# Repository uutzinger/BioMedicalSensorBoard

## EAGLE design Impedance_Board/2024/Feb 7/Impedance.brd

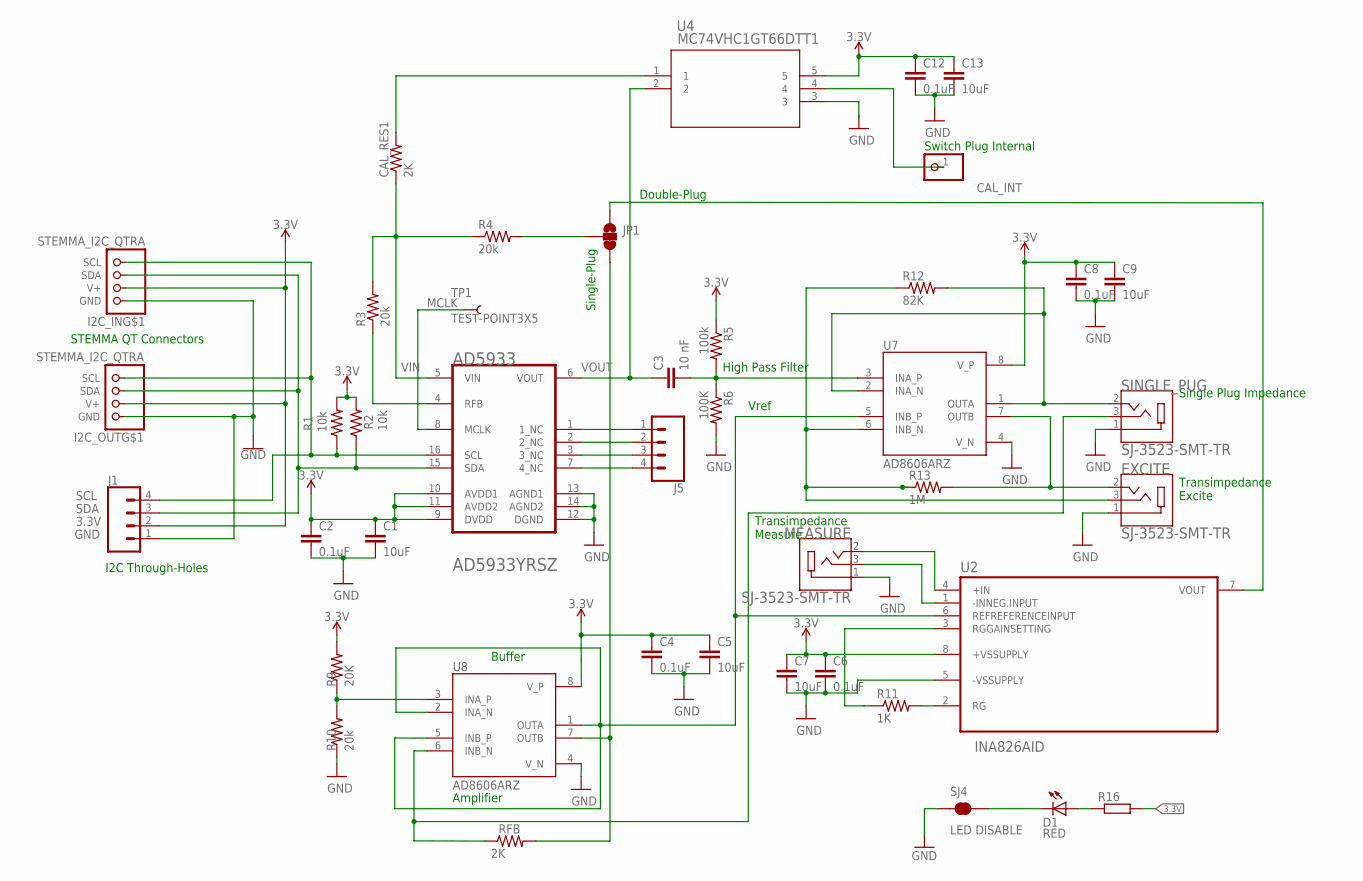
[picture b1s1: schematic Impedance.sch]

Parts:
AD5933: ANALOG_DEVICES_AD5933YRSZANALOG_DEVICES_AD5933YRS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; ANALOG_DEVICES_AD5933YRSZ_0
C1, C5, C7, C9, C13: 10uF; C0603
C2, C4, C6, C8, C12: 0.1uF; C0603
C3: 10 nF; C0603
CAL_INT: PINHD-1X1; 1X01
CAL_RES1: 2K; R0603
D1: RED; LED-0603
EXCITE: SJ-3523-SMT-TR; CUI_SJ-3523-SMT-TR
I2C_IN, I2C_OUT: STEMMA_I2C_QTRA; JST_SH4_RA
J1, J5: CONN_04; 1X04
JP1: JUMPER-SMT_3_1-NC_TRACE_NO-SILK; SMT-JUMPER_3_1-NC_TRACE_NO-SILK
MEASURE: SJ-3523-SMT-TR; CUI_SJ-3523-SMT-TR
R1, R2: 10k; R0603
R3, R4, R10: 20k; R0603
R5: 100k; R0603
R6: 100K; R0603
R9: 20K; R0603
R11: 1K; R0603
R12: 82K; R0603
R13: 1M; R0603
R16: R__0603; R0603
RFB: 2K; R0603
SINGLE_PUG: SJ-3523-SMT-TR; CUI_SJ-3523-SMT-TR
SJ4: LED DISABLE; SMT-JUMPER_2_NC_TRACE_NO-SILK
TP1: TEST-POINT3X5; PAD.03X.05
U2: INA826AID; SOIC127P599X175-8N
U4: MC74VHC1GT66DTT1; TSOP5_1P65X3P15_ONS
U7, U8: AD8606ARZ; SOIC127P600X175-8N

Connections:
3.3V: AD5933.9 (DVDD), AD5933.10 (AVDD1), AD5933.11 (AVDD2), C1.1, C2.1, C4.1, C5.1, C6.1, C7.1, C8.1, C9.1, C12.1, C13.1, I2C_IN.2 (V+), I2C_OUT.2 (V+), J1.2, R1.2, R2.2, R5.1, R9.2, R16.2, U2.8 (+VSSUPPLY), U4.5, U7.8 (V_P), U8.8 (V_P)
GND: AD5933.12 (DGND), AD5933.13 (AGND1), AD5933.14 (AGND2), C1.2, C2.2, C4.2, C5.2, C6.2, C7.2, C8.2, C9.2, C12.2, C13.2, EXCITE.1, I2C_IN.1 (GND), I2C_OUT.1 (GND), J1.1, MEASURE.1, R6.2, R10.1, SINGLE_PUG.1, SJ4.1, U2.5 (-VSSUPPLY), U4.3, U7.4 (V_N), U8.4 (V_N)
MCLK: AD5933.8 (MCLK), TP1.P$1
unnamed: JP1.2, R4.2
unnamed: CAL_INT.1, U4.4
unnamed: AD5933.1 (1_NC), J5.1
unnamed: AD5933.2 (2_NC), J5.2
unnamed: AD5933.4 (RFB), R3.1
unnamed: RFB.2, U8.7 (OUTB)
unnamed: C3.2, R5.2, R6.1, U7.3 (INA_P)
unnamed: AD5933.3 (3_NC), J5.3
unnamed: AD5933.7 (4_NC), J5.4
unnamed: U2.6 (REFREFERENCEINPUT), U7.5 (INB_P), U8.1 (OUTA), U8.2 (INA_N), U8.5 (INB_P)
unnamed: R9.1, R10.2, U8.3 (INA_P)
unnamed: R12.2, SINGLE_PUG.2, U7.1 (OUTA), U7.2 (INA_N)
unnamed: R11.1, U2.3 (RGGAINSETTING)
unnamed: RFB.1, SINGLE_PUG.3, U8.6 (INB_N)
unnamed: R11.2, U2.2 (RG)
unnamed: EXCITE.2, R13.2, U7.7 (OUTB)
unnamed: MEASURE.2, U2.4 (+IN)
unnamed: MEASURE.3, U2.1 (-INNEG.INPUT)
unnamed: EXCITE.3, R12.1, R13.1, U7.6 (INB_N)
unnamed: CAL_RES1.2, U4.1
unnamed: JP1.1, U2.7 (VOUT)
unnamed: D1.A, R16.1
unnamed: D1.C, SJ4.2
SCL: AD5933.16 (SCL), I2C_IN.4 (SCL), I2C_OUT.4 (SCL), J1.4, R1.1
SDA: AD5933.15 (SDA), I2C_IN.3 (SDA), I2C_OUT.3 (SDA), J1.3, R2.1
VIN: AD5933.5 (VIN), CAL_RES1.1, R3.2, R4.1
VOUT: AD5933.6 (VOUT), C3.1, U4.2

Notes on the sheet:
High Pass Filter
Vref
Transimpedance Measure
Transimpedance Excite
Single Plug Impedance
Amplifier
Buffer
STEMMA QT Connectors
I2C Through-Holes
Single-Plug
Double-Plug
Switch Plug Internal

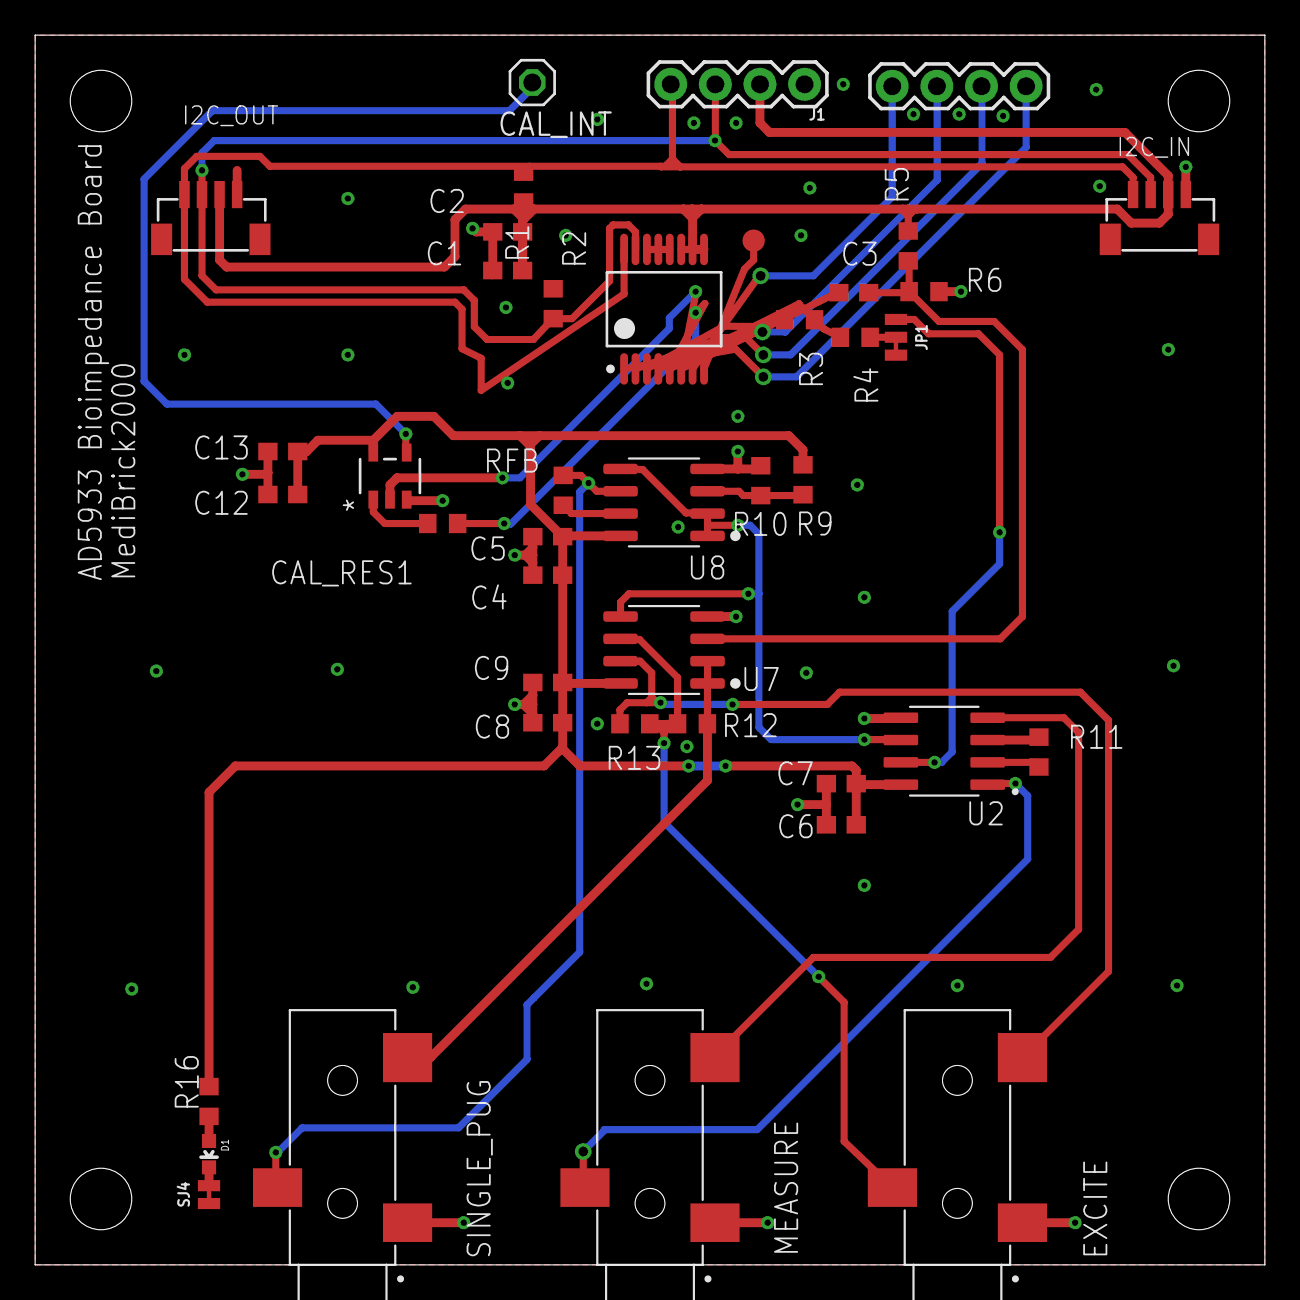
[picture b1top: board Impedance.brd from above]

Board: 2 copper layers, 70.0 x 70.0 mm, 42 parts (0 on the bottom side), 30 nets.

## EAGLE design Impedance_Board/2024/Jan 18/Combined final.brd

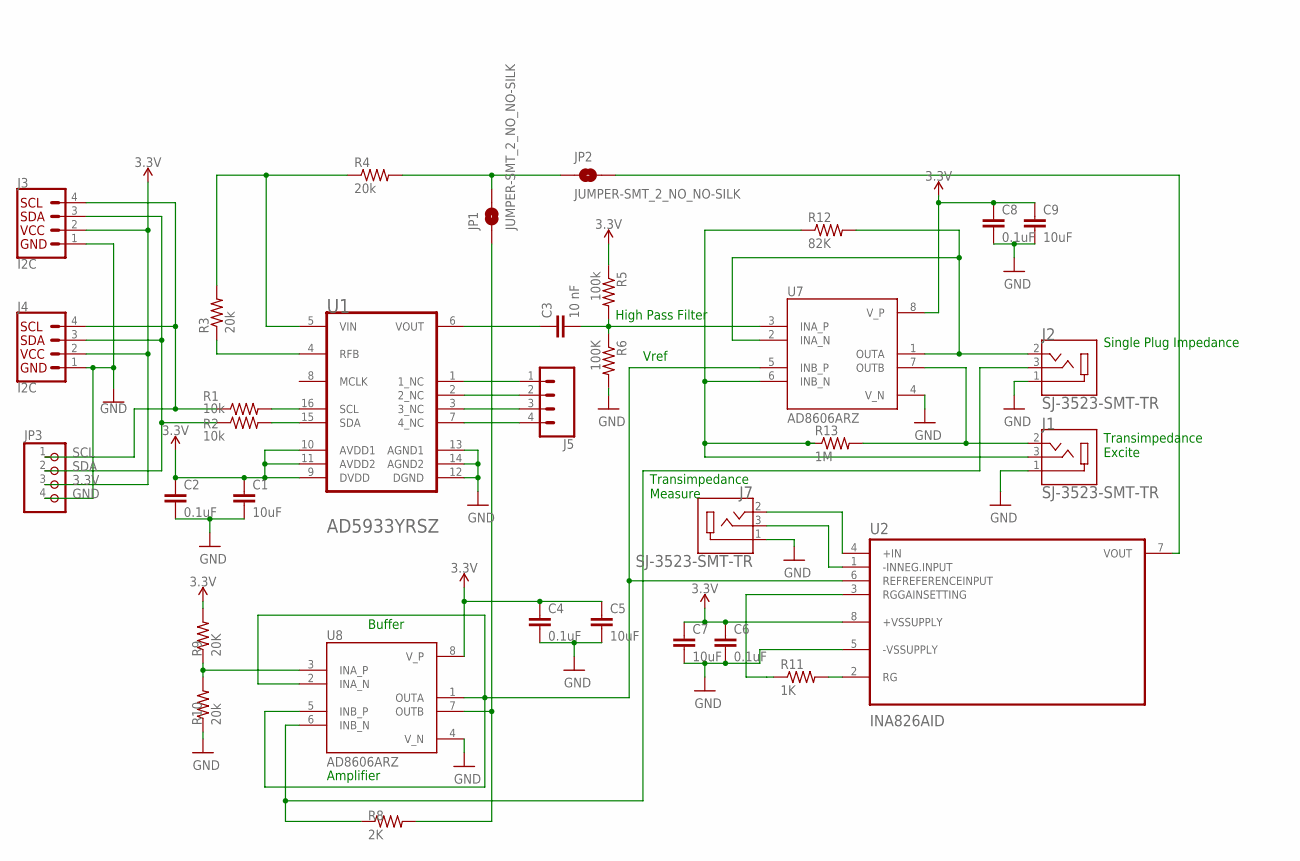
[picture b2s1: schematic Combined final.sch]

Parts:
C1, C5, C7, C9: 10uF; C0603
C2, C4, C6, C8: 0.1uF; C0603
C3: 10 nF; C0603
J1, J2, J7: SJ-3523-SMT-TR; CUI_SJ-3523-SMT-TR
J3, J4: I2C; JST04_1MM_RA
J5: CONN_04; 1X04
JP1, JP2: JUMPER-SMT_2_NO_NO-SILK; SMT-JUMPER_2_NO_NO-SILK
JP3: PINHD-1X4; 1X04
R1, R2: 10k; R0603
R3, R4, R10: 20k; R0603
R5: 100k; R0603
R6: 100K; R0603
R8: 2K; R0603
R9: 20K; R0603
R11: 1K; R0603
R12: 82K; R0603
R13: 1M; R0603
U1: ANALOG_DEVICES_AD5933YRSZANALOG_DEVICES_AD5933YRS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; ANALOG_DEVICES_AD5933YRSZ_0
U2: INA826AID; SOIC127P599X175-8N
U7, U8: AD8606ARZ; SOIC127P600X175-8N

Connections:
3.3V: C1.1, C2.1, C4.1, C5.1, C6.1, C7.1, C8.1, C9.1, J3.2, J4.2, JP3.3, R5.1, R9.2, U1.9 (DVDD), U1.10 (AVDD1), U1.11 (AVDD2), U2.8 (+VSSUPPLY), U7.8 (V_P), U8.8 (V_P)
GND: C1.2, C2.2, C4.2, C5.2, C6.2, C7.2, C8.2, C9.2, J1.1, J2.1, J3.1, J4.1, J7.1, JP3.4, R6.2, R10.1, U1.12 (DGND), U1.13 (AGND1), U1.14 (AGND2), U2.5 (-VSSUPPLY), U7.4 (V_N), U8.4 (V_N)
unnamed: R1.2, U1.16 (SCL)
unnamed: R2.2, U1.15 (SDA)
unnamed: J5.1, U1.1 (1_NC)
unnamed: J5.2, U1.2 (2_NC)
unnamed: R3.1, U1.4 (RFB)
unnamed: R3.2, R4.1, U1.5 (VIN)
unnamed: JP1.2, JP2.1, R4.2
unnamed: C3.1, U1.6 (VOUT)
unnamed: C3.2, R5.2, R6.1, U7.3 (INA_P)
unnamed: J5.3, U1.3 (3_NC)
unnamed: J5.4, U1.7 (4_NC)
unnamed: JP1.1, R8.2, U8.7 (OUTB)
unnamed: U2.6 (REFREFERENCEINPUT), U7.5 (INB_P), U8.1 (OUTA), U8.2 (INA_N), U8.5 (INB_P)
unnamed: R9.1, R10.2, U8.3 (INA_P)
unnamed: J2.2, R12.2, U7.1 (OUTA), U7.2 (INA_N)
unnamed: R11.1, U2.3 (RGGAINSETTING)
unnamed: J2.3, R8.1, U8.6 (INB_N)
unnamed: R11.2, U2.2 (RG)
unnamed: J1.2, R13.2, U7.7 (OUTB)
unnamed: J7.2, U2.4 (+IN)
unnamed: J7.3, U2.1 (-INNEG.INPUT)
unnamed: J1.3, R12.1, R13.1, U7.6 (INB_N)
unnamed: JP2.2, U2.7 (VOUT)
SCL: J3.4, J4.4, JP3.1, R1.1
SDA: J3.3, J4.3, JP3.2, R2.1

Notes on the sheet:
High Pass Filter
Vref
Transimpedance Measure
Transimpedance Excite
Single Plug Impedance
Amplifier
Buffer

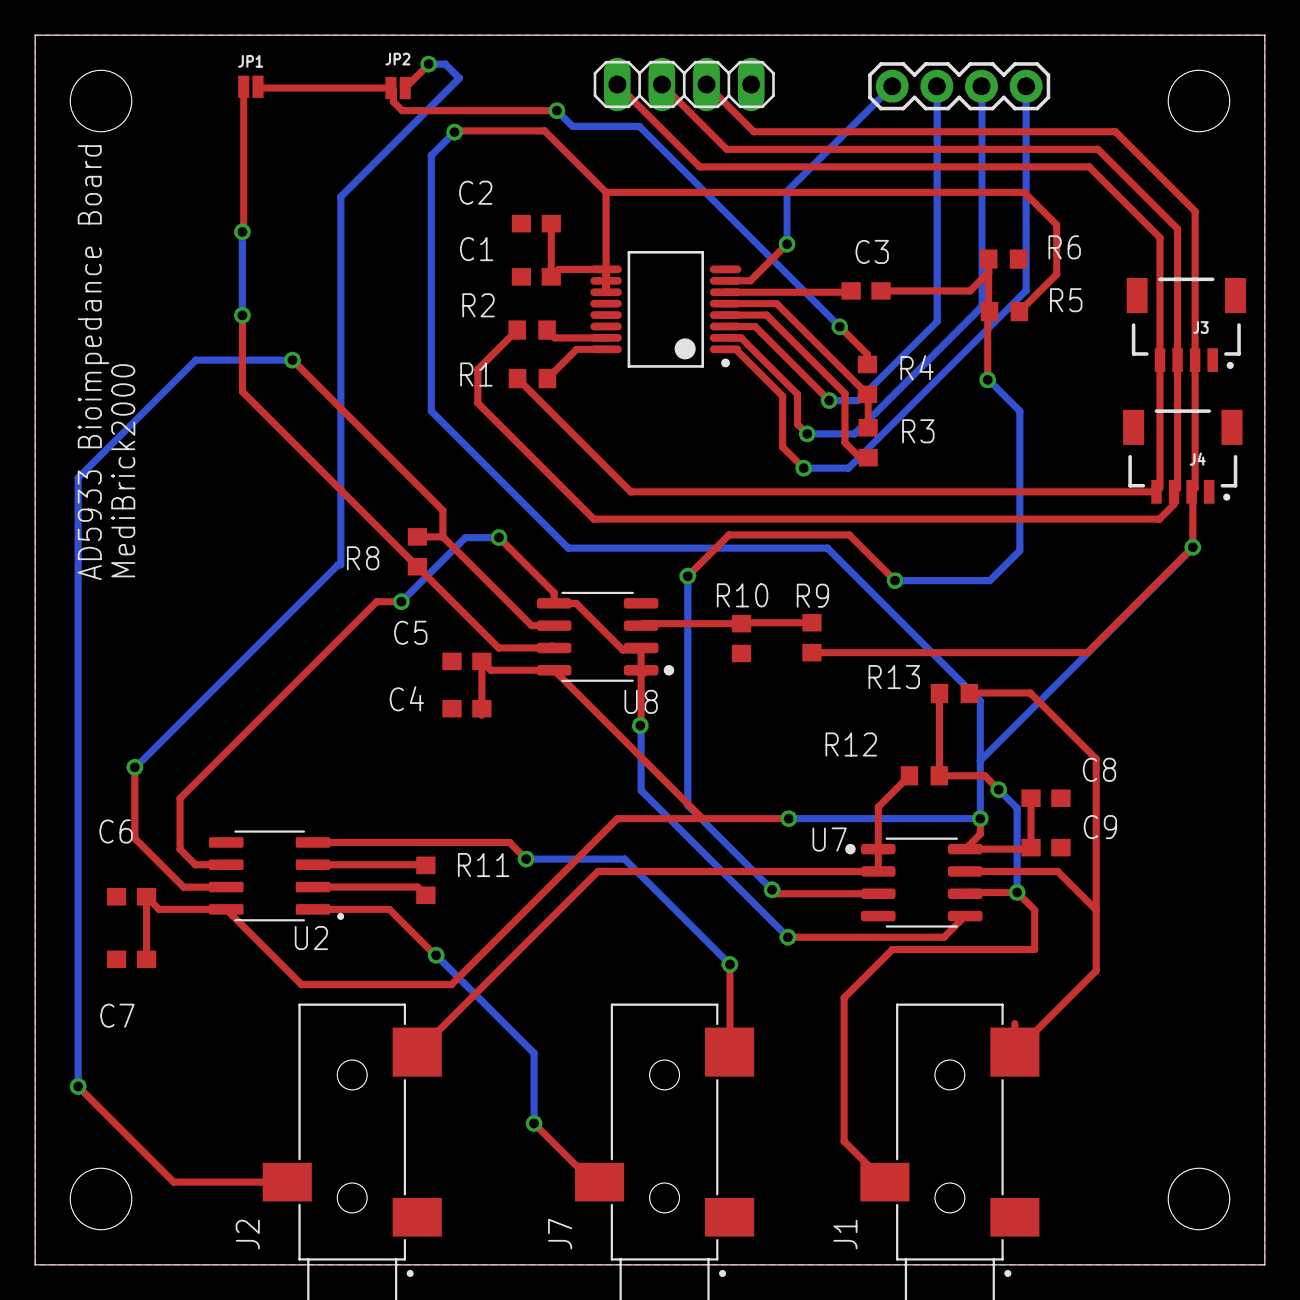
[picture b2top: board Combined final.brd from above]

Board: 2 copper layers, 70.0 x 70.0 mm, 34 parts (0 on the bottom side), 27 nets.

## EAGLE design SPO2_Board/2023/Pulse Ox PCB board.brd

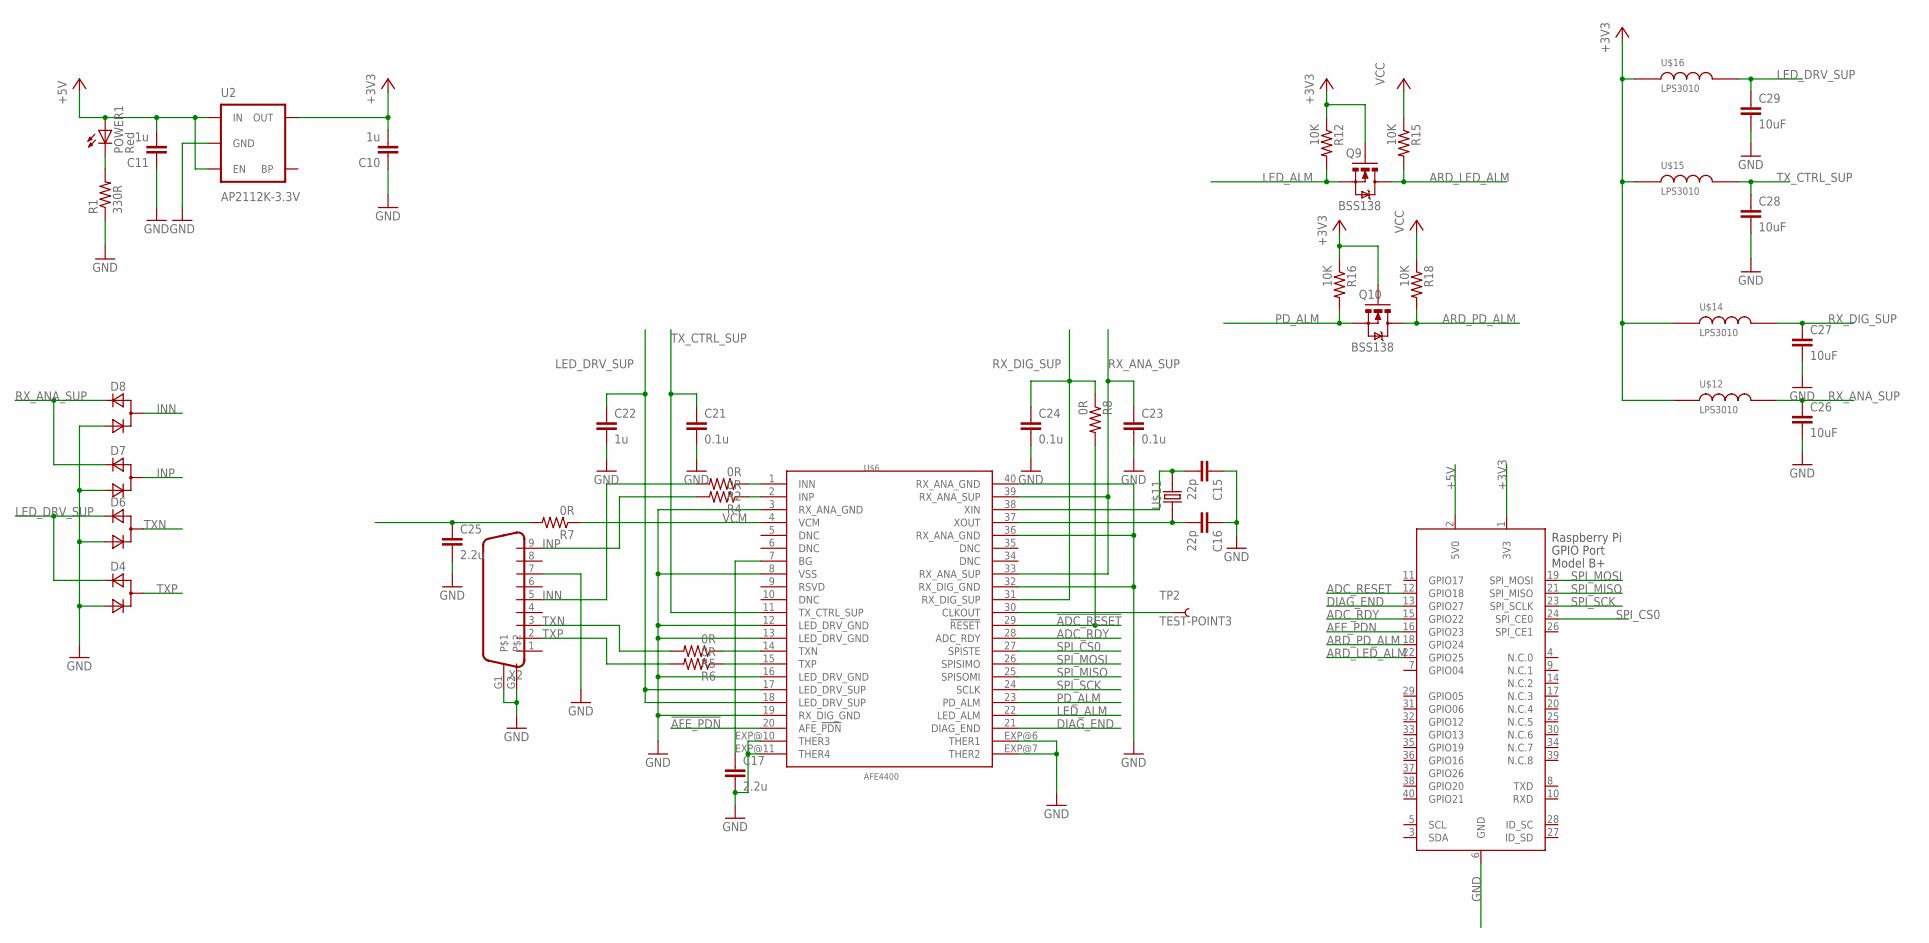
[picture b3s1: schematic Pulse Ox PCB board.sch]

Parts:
C10, C11, C22: 1u; C0805
C15, C16: 22p; C0402
C17, C25: 2.2u; C0402
C21, C23, C24: 0.1u; C0805
C26, C27, C28, C29: 10uF; C0805
D4, D6, D7, D8: D_ACACSOT323; SOT323
POWER1: Red; CHIPLED_0603
Q9, Q10: BSS138; SOT23-3
R1: 330R; R0805
R2, R4, R7: 0R; R0402
R5, R6, R8: 0R; R0805
R12, R15, R16, R18: 10K; 0805
TP2: TEST-POINT3; PAD.03X.03
U2: AP2112K-3.3V; SOT23-5
U$6: AFE4400; QFN-40
U$11: ABM3
U$12, U$14, U$15, U$16: LPS3010; LPS
X2: DB9
X3: RASPI_BOARD_B+_HD; RASPI_BOARD_B+HAT_DF

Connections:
!ADC_RESET: R8.2, U$6.29 (!RESET)
!AFE_PDN: U$6.20 (AFE_!PDN)
+3V3: C10.2, Q9.1 (G), Q10.1 (G), R12.1, R16.1, U2.5 (OUT), U$12.1, U$14.1, U$15.1, U$16.1, X3.1 (3V3)
+5V: C11.2, POWER1.A, U2.1 (IN), U2.3 (EN), X3.2 (5V0)
ADC_RDY: U$6.28 (ADC_RDY), X3.15 (GPIO22)
ADC_RESET: X3.12 (GPIO18)
AFE_PDN: X3.16 (GPIO23)
ARD_LED_ALM: Q9.3 (D), R15.2, X3.22 (GPIO25)
ARD_PD_ALM: Q10.3 (D), R18.2, X3.18 (GPIO24)
DIAG_END: U$6.21 (DIAG_END), X3.13 (GPIO27)
GND: C10.1, C11.1, C15.1, C16.1, C17.2, C21.2, C22.2, C23.2, C24.2, C25.2, C26.2, C27.2, C28.2, C29.2, D4.2 (C), D6.2 (C), D7.2 (C), D8.2 (C), R1.1, U2.2 (GND), U$6.3 (RX_ANA_GND), U$6.8 (VSS), U$6.12 (LED_DRV_GND), U$6.13 (LED_DRV_GND), U$6.16 (LED_DRV_GND), U$6.19 (RX_DIG_GND), U$6.32 (RX_DIG_GND), U$6.36 (RX_ANA_GND), U$6.40 (RX_ANA_GND), U$6.EXP@6 (THER1), U$6.EXP@7 (THER2), U$6.EXP@10 (THER3), U$6.EXP@11 (THER4), X2.7, X2.G1, X2.G2, X3.6 (GND)
INN: D8.1 (CA), R2.2, X2.5
INP: D7.1 (CA), R4.2, X2.9
LED_ALM: Q9.2 (S), R12.2, U$6.22 (LED_ALM)
LED_DRV_SUP: C22.1, C29.1, D4.3 (A), D6.3 (A), U$6.17 (LED_DRV_SUP), U$6.18 (LED_DRV_SUP), U$16.2
unnamed: POWER1.C, R1.2
unnamed: C15.2, U$6.38 (XIN), U$11.2
unnamed: C16.2, U$6.37 (XOUT), U$11.1
unnamed: C17.1, U$6.7 (BG)
unnamed: TP2.P$1, U$6.30 (CLKOUT)
unnamed: R2.1, U$6.1 (INN)
unnamed: R4.1, U$6.2 (INP)
unnamed: C25.1, R7.2
P14: R5.1, U$6.14 (TXN)
P15: R6.1, U$6.15 (TXP)
PD_ALM: Q10.2 (S), R16.2, U$6.23 (PD_ALM)
RX_ANA_SUP: C23.1, C26.1, D7.3 (A), D8.3 (A), U$6.33 (RX_ANA_SUP), U$6.39 (RX_ANA_SUP), U$12.2
RX_DIG_SUP: C24.1, C27.1, R8.1, U$6.31 (RX_DIG_SUP), U$14.2
SPI_CS0: U$6.27 (SPISTE), X3.24 (SPI_CE0)
SPI_MISO: U$6.25 (SPISOMI), X3.21 (SPI_MISO)
SPI_MOSI: U$6.26 (SPISIMO), X3.19 (SPI_MOSI)
SPI_SCK: U$6.24 (SCLK), X3.23 (SPI_SCLK)
TXN: D6.1 (CA), R5.2, X2.3
TXP: D4.1 (CA), R6.2, X2.2
TX_CTRL_SUP: C21.1, C28.1, U$6.11 (TX_CTRL_SUP), U$15.2
VCC: R15.1, R18.1
VCM: R7.1, U$6.4 (VCM)

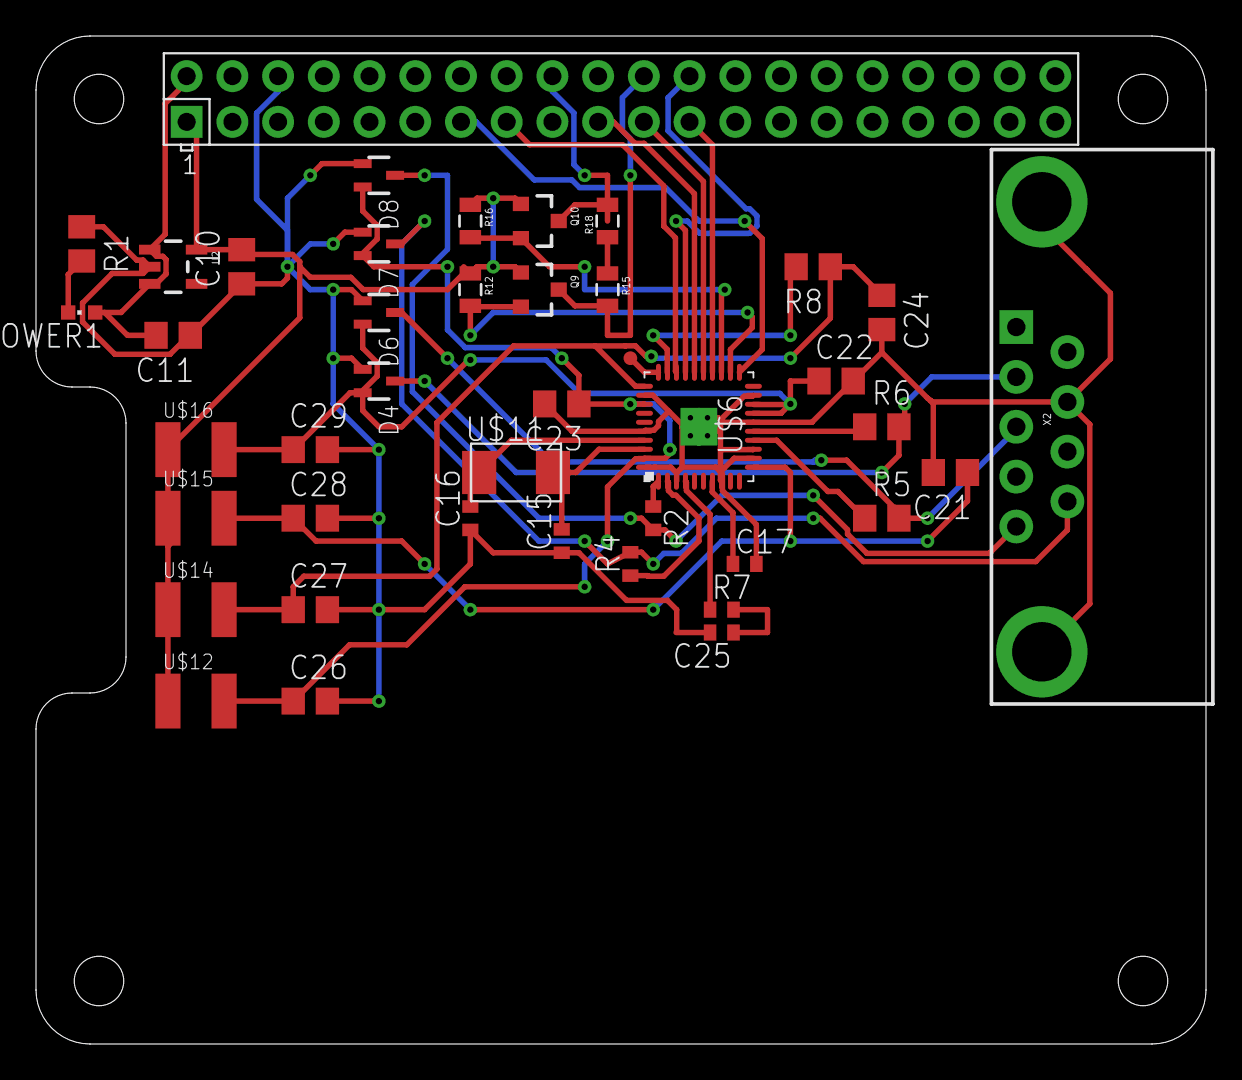
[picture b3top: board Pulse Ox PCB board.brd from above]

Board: 2 copper layers, 65.0 x 56.0 mm, 42 parts (0 on the bottom side), 34 nets.

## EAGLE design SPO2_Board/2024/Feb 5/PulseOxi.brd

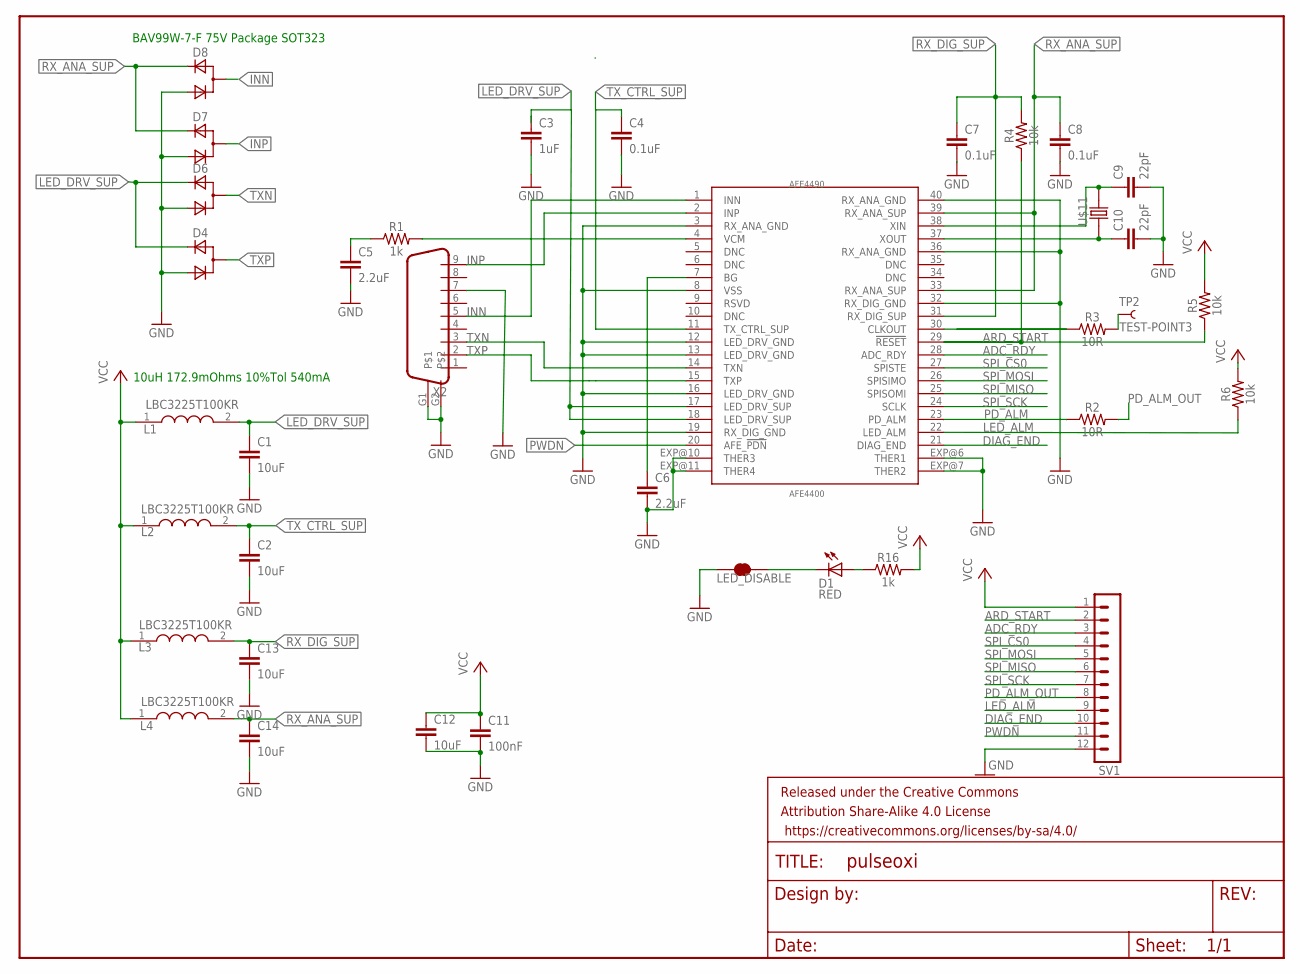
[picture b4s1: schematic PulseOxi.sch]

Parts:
AFE4490: AFE4400; QFN-40
C1, C2, C12, C13, C14: 10uF; 0603
C3: 1uF; 0603
C4, C7, C8: 0.1uF; 0603
C5, C6: 2.2uF; 0603
C9, C10: 22pF; 0603
C11: 100nF; 0603
D1: RED; LED-0603
D4, D6, D7, D8: D_ACACSOT323; SOT323
FRAME1: FRAME-LETTERNO_PACKAGE; DUMMY
L1, L2, L3, L4: LBC3225T100KR; INDC3225X270N
LED_DISABLE: JUMPER-SMT_2_NC_TRACE_SILK; SMT-JUMPER_2_NC_TRACE_SILK
R1, R16: 1k; 0603
R2, R3: 10R; 0603
R4, R5, R6: 10k; 0603
SV1: MA12-1
TP2: TEST-POINT3; PAD.03X.03
U$11: ABM3
X2: DB9

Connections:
ADC_RDY: AFE4490.28 (ADC_RDY), SV1.3
ARD_START: AFE4490.29 (!RESET), R4.1, R5.1, SV1.2
DIAG_END: AFE4490.21 (DIAG_END), SV1.10
GND: AFE4490.3 (RX_ANA_GND), AFE4490.8 (VSS), AFE4490.12 (LED_DRV_GND), AFE4490.13 (LED_DRV_GND), AFE4490.16 (LED_DRV_GND), AFE4490.19 (RX_DIG_GND), AFE4490.32 (RX_DIG_GND), AFE4490.36 (RX_ANA_GND), AFE4490.40 (RX_ANA_GND), AFE4490.EXP@6 (THER1), AFE4490.EXP@7 (THER2), AFE4490.EXP@10 (THER3), AFE4490.EXP@11 (THER4), C1.2, C2.2, C3.2, C4.2, C5.2, C6.2, C7.2, C8.2, C9.2, C10.2, C11.2, C12.2, C13.2, C14.2, D4.2 (C), D6.2 (C), D7.2 (C), D8.2 (C), LED_DISABLE.1, SV1.12, X2.7, X2.G1, X2.G2
INN: AFE4490.1 (INN), D8.1 (CA), X2.5
INP: AFE4490.2 (INP), D7.1 (CA), X2.9
LED_ALM: AFE4490.22 (LED_ALM), R6.1, SV1.9
LED_DRV_SUP: AFE4490.17 (LED_DRV_SUP), AFE4490.18 (LED_DRV_SUP), C1.1, C3.1, D4.3 (A), D6.3 (A), L1.2
unnamed: R3.2, TP2.P$1
unnamed: AFE4490.30 (CLKOUT), R3.1
unnamed: AFE4490.4 (VCM), R1.2
unnamed: C5.1, R1.1
unnamed: AFE4490.38 (XIN), C9.1, U$11.2
unnamed: AFE4490.37 (XOUT), C10.1, U$11.1
unnamed: AFE4490.7 (BG), C6.1
unnamed: D1.A, R16.1
unnamed: D1.C, LED_DISABLE.2
PD_ALM: AFE4490.23 (PD_ALM), R2.1
PD_ALM_OUT: R2.2, SV1.8
PWDN: AFE4490.20 (AFE_!PDN), SV1.11
RX_ANA_SUP: AFE4490.33 (RX_ANA_SUP), AFE4490.39 (RX_ANA_SUP), C8.1, C14.1, D7.3 (A), D8.3 (A), L4.2
RX_DIG_SUP: AFE4490.31 (RX_DIG_SUP), C7.1, C13.1, L3.2, R4.2
SPI_CS0: AFE4490.27 (SPISTE), SV1.4
SPI_MISO: AFE4490.25 (SPISOMI), SV1.6
SPI_MOSI: AFE4490.26 (SPISIMO), SV1.5
SPI_SCK: AFE4490.24 (SCLK), SV1.7
TXN: AFE4490.14 (TXN), D6.1 (CA), X2.3
TXP: AFE4490.15 (TXP), D4.1 (CA), X2.2
TX_CTRL_SUP: AFE4490.11 (TX_CTRL_SUP), C2.1, C4.1, L2.2
VCC: C11.1, C12.1, L1.1, L2.1, L3.1, L4.1, R5.2, R6.2, R16.2, SV1.1

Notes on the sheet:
BAV99W-7-F 75V Package SOT323
10uH 172.9mOhms 10%Tol 540mA

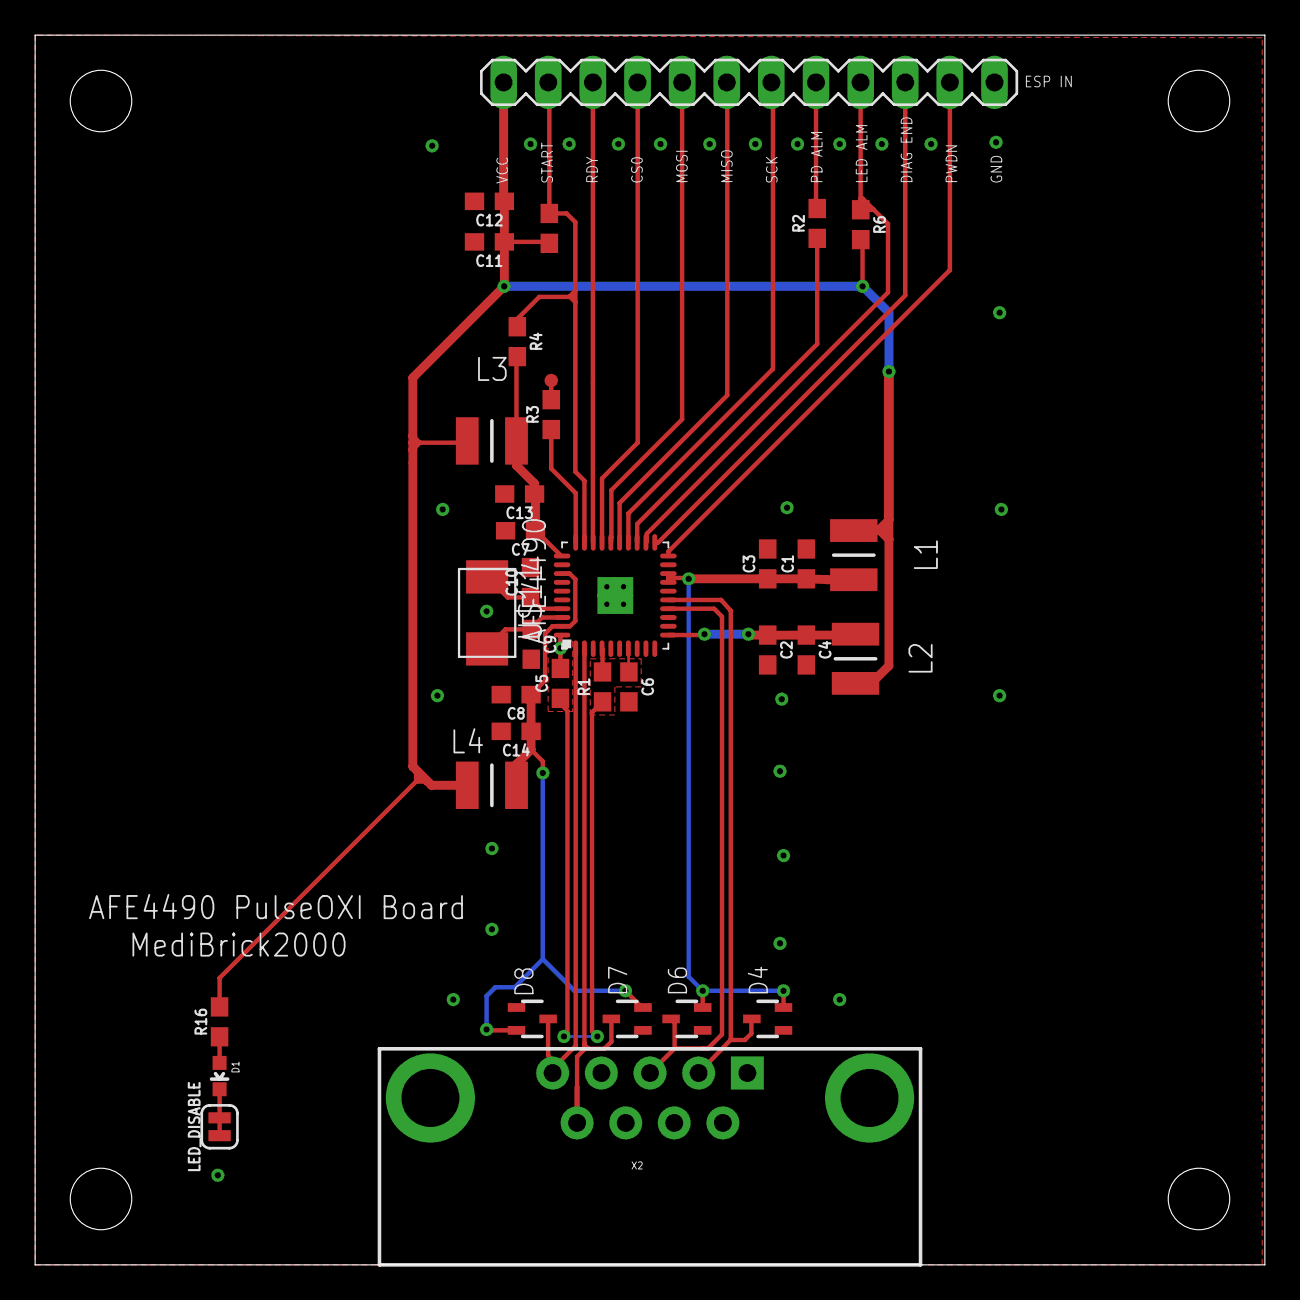
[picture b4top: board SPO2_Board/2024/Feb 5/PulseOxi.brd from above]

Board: 2 copper layers, 70.0 x 70.0 mm, 37 parts (0 on the bottom side), 30 nets.

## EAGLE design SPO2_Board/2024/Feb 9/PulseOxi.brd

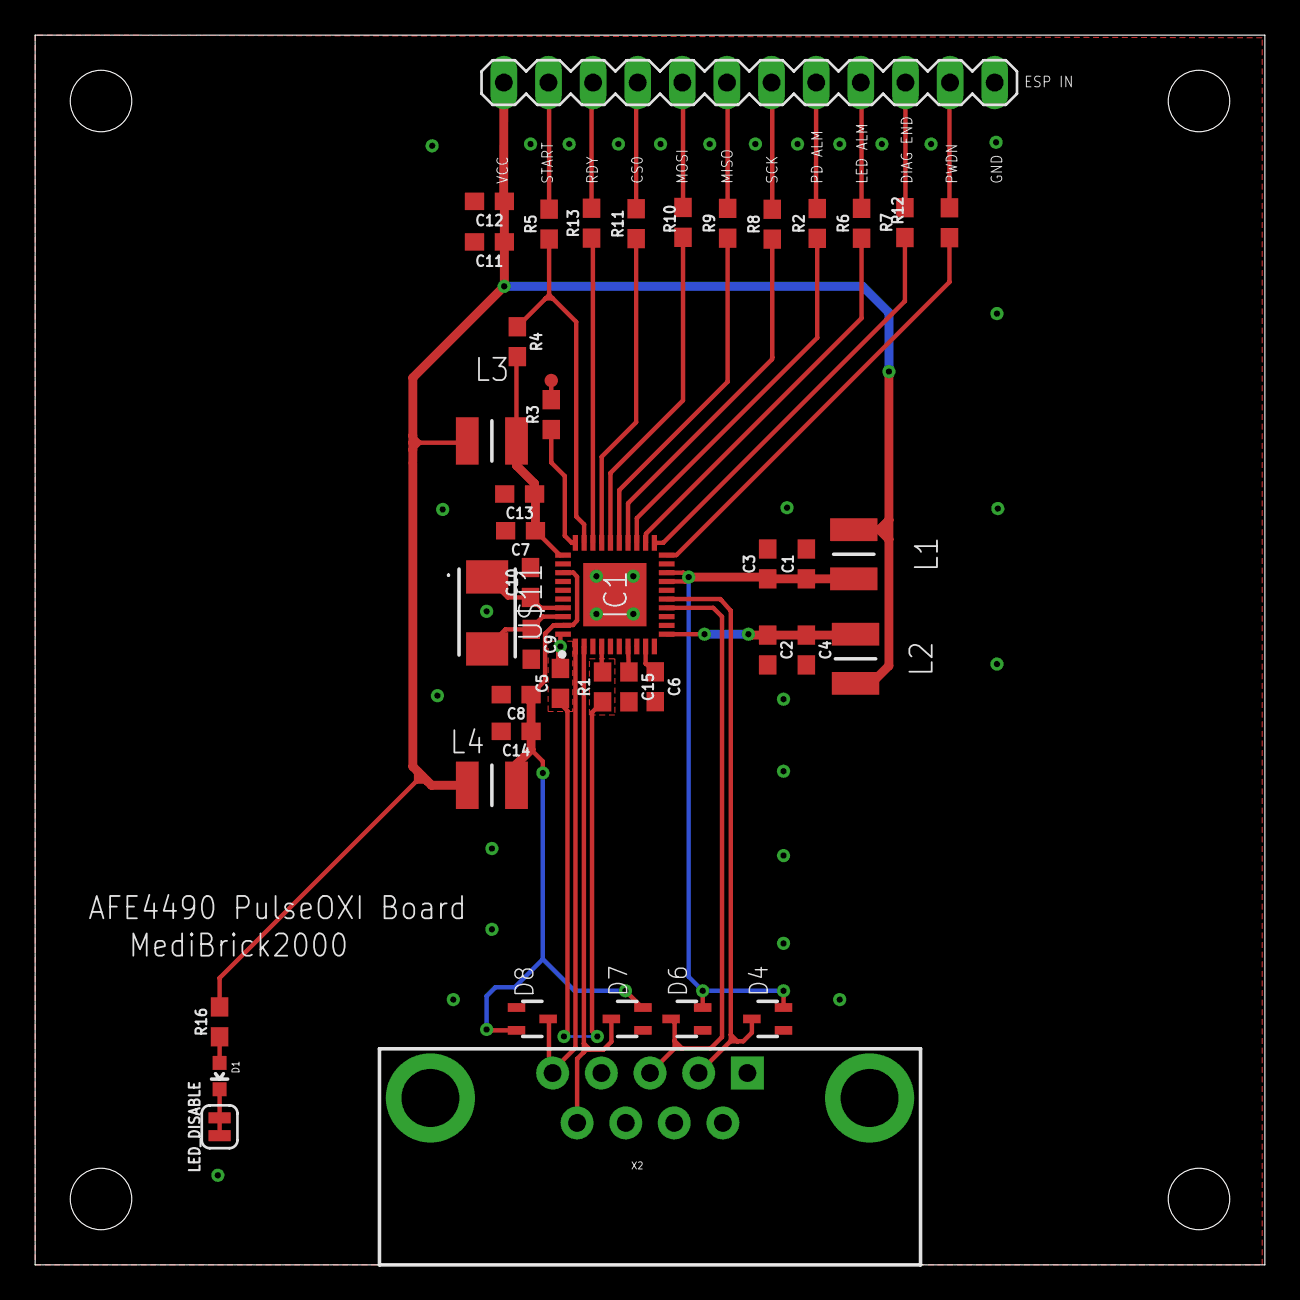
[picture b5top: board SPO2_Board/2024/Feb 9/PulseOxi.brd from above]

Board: 2 copper layers, 70.0 x 70.0 mm, 45 parts (0 on the bottom side), 40 nets.

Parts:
C1, C2, C12, C13, C14: 10uF; 0603
C3: 1uF; 0603
C4, C7, C8: 0.1uF; 0603
C5: 10nF; 0603
C6, C15: 2.2uF; 0603
C9, C10: 18pF; 0603
C11: 100nF; 0603
D1: RED; LED-0603
D4, D6, D7, D8: SOT323
FRAME1: FRAME-LETTERNO_PACKAGE; DUMMY
IC1: AFE4400RHAR; QFN50P600X600X100-41N
L1, L2, L3, L4: LBC3225T100KR; INDC3225X270N
LED_DISABLE: JUMPER-SMT_2_NC_TRACE_SILK; SMT-JUMPER_2_NC_TRACE_SILK
R1, R16: 1k; 0603
R2, R3, R5, R6, R7, R8, R9, R10, R11, R12, R13: 10R; 0603
R4: 10k; 0603
SV1: MA12-1
TP2: TEST-POINT3; PAD.03X.03
U$11: ABM3-8.000MHZ-D2Y-T; ABM3
X2: DB9

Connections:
ADCRDY: R13.2, SV1.3
AFE_PWDN: IC1.20, R12.1
CS: R11.2, SV1.4
DIAGEND: R7.2, SV1.10
GND: C1.2, C2.2, C3.2, C4.2, C5.2, C6.2, C7.2, C8.2, C9.2, C10.2, C11.2, C12.2, C13.2, C14.2, C15.2, D4.2, D6.2, D7.2, D8.2, IC1.3, IC1.8, IC1.12, IC1.13, IC1.16, IC1.19, IC1.32, IC1.36, IC1.40, IC1.41, LED_DISABLE.1, SV1.12, X2.7, X2.G1, X2.G2
INN: D8.1, IC1.1, X2.5
INP: D7.1, IC1.2, X2.9
LEDALARM: R6.2, SV1.9
LED_DRV_SUP: C1.1, C3.1, D4.3, D6.3, IC1.17, IC1.18, L1.2
MISO: R9.2, SV1.6
MOSI: R10.2, SV1.5
unnamed: R3.2, TP2.P$1
unnamed: IC1.30, R3.1
unnamed: IC1.29, R4.1, R5.1
unnamed: C15.1, IC1.7
unnamed: C5.1, R1.1
unnamed: C6.1, IC1.9
unnamed: IC1.28, R13.1
unnamed: IC1.21, R7.1
unnamed: IC1.22, R6.1
unnamed: IC1.23, R2.1
unnamed: IC1.24, R8.1
unnamed: IC1.25, R9.1
unnamed: IC1.26, R10.1
unnamed: IC1.27, R11.1
unnamed: C9.1, IC1.38, U$11.2
unnamed: IC1.4, R1.2
unnamed: C10.1, IC1.37, U$11.1
unnamed: D1.A, R16.1
unnamed: D1.C, LED_DISABLE.2
PD_ALM_OUT: R2.2, SV1.8
PWDN: R12.2, SV1.11
RESET: R5.2, SV1.2
RX_ANA_SUP: C8.1, C14.1, D7.3, D8.3, IC1.33, IC1.39, L4.2
RX_DIG_SUP: C7.1, C13.1, IC1.31, L3.2, R4.2
SCK: R8.2, SV1.7
TXN: D6.1, IC1.14, X2.3
TXP: D4.1, IC1.15, X2.2
TX_CTRL_SUP: C2.1, C4.1, IC1.11, L2.2
VCC: C11.1, C12.1, L1.1, L2.1, L3.1, L4.1, R16.2, SV1.1

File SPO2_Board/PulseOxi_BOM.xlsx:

Item # | Designator | Qty | Manufacturer | Mfg Part # | LCSC Part# | U.S. Distributor | Description / Value | *Package/Footprint | Mounting Type | Your Instructions / Notes
1 | C1,C2,C12,C13,C14 | 5 | Samsung Electro-Mechanics | CL10A106MA8NRNC | C96446 |  | 10uF | 0603 | SMD
2 | C3 | 1 | Samsung Electro-Mechanics | CL10A105KB8NNNC | C15849 |  | 1uF | 0603 | SMD
3 | C4,C7,C8 | 3 | Samsung Electro-Mechanics | CL10B104KB8NNNC | C1591 |  | 0.1uF | 0603 | SMD
4 | C5 | 1 | Samsung Electro-Mechanics | CL10B103KB8NNNC | C1589 |  | 10nF | 0603
5 | C6,C15 | 2 | Samsung Electro-Mechanics | CL10B222KB8NNNC | C16033 |  | 2.2uF | 0603 | SMD
6 | C10,C9 | 2 | Samsung Electro-Mechanics | CL10C180JB8NNNC | C1647 |  | 18pF | 0603 | SMD
7 | C11 | 1 | Samsung Electro-Mechanics | CL10B104KB8NNNC | C1591 |  | 100nF | 0603 | SMD
8 | D1 | 1 | XINGLIGHT | XL-1608UBC-04 | C965807 |  | BLUE LED | 0603 | SMD
9 | D4,D6,D7,D8 | 4 | Diodes Incorporated | BAV99W-7-F | C93035 |  | Schottky Barrier Diodes | SOT-323 | SMD
10 | IC1 | 1 | Texas Instruments | AFE4490RHAR | C2651608 | https://www.mouser.com/ProductDetail/Texas-Instruments/AFE44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 | Analog Front End (AFEs) | VQFN-40 | SMD
11 | L1,L2,L3,L4 | 4 | Taiyo Yuden | LBC3225T100KR | C223424 |  | INDUCTOR 10uH | 1210 | SMD
12 | R1,R16 | 2 | YAGEO | RC0603FR-071KL | C22548 |  | 1K | 0603 | SMD
13 | R2,R3,R5,R6,R7,R8,R9,R10,R11,R12,R13 | 11 | YAGEO | AC0603FR-0710RL | C138286 |  | 10 | 0603 | SMD
14 | R4 | 1 | YAGEO | RC0603FR-0710KL | C98220 |  | 10K | 0603
15 | OSC | 1 | Abracon LLC | ABM3-8.000MHZ-D2Y-T | C144380 |  | Oscillator, 8MHz | 5032 | SMD
16 | X2 | 1 | TE Connectivity | 2301843-1 | C3118153 |  | DB9 CONNECTOR | Tray | Throughole

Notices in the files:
parts and their libraries:
SparkFun-Jumpers: Licensing: Creative Commons ShareAlike 4.0 International - https://creativecommons.org/licenses/by-sa/4.0
MC74VHC1GT66DTT1: COPYRIGHT: Copyright (C) 2024 Ultra Librarian. All rights reserved.
SparkFun-Aesthetics: https://creativecommons.org/licenses/by-sa/4.0
